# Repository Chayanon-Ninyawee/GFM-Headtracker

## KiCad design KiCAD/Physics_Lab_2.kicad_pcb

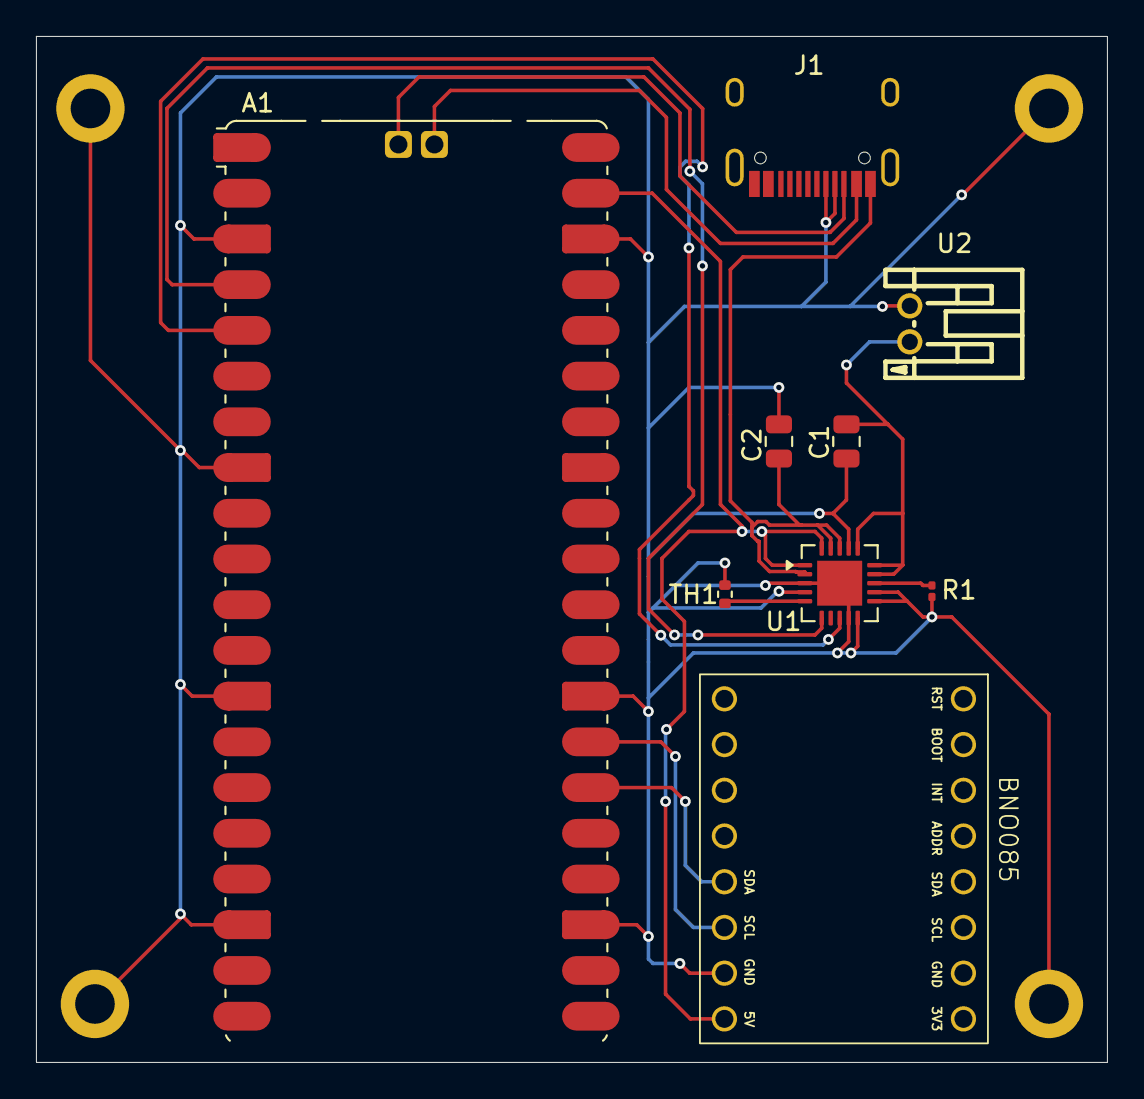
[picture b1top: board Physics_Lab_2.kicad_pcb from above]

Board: 2 copper layers, 59.5 x 57.0 mm, 9 parts (0 on the bottom side), 12 nets.

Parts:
A1: RaspberryPi_Pico_W; RaspberryPi_Pico_W_SMD
BNO085_Halley1: BNO085 Halley
C1: 4.7uF; C_0805_2012Metric
C2: 10uF; C_0805_2012Metric
J1: USB_C; HRO-TYPE-C-31-M-12
R1: 2K; R_0201_0603Metric
TH1: 10kΩ; R_0402_1005Metric
U1: MCP73871; QFN-20-1EP_4x4mm_P0.5mm_EP2.5x2.5mm
U2: S2B-PH-K-S-GW; CONN-TH_S2B-PH-K-S-GW

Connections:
GND: A1.3 (GND), A1.8 (GND), A1.13 (GND), A1.18 (GND), A1.23 (GND), A1.28 (GND), A1.38 (GND), BNO085_Halley1.15 (GND), C1.2, C2.1, J1.4 (GND), J1.5 (Shield), R1.1, TH1.1, U1.3 (SEL), U1.4 (PROG2), U1.9 (~TE), U1.10 (V_{SS}), U1.11 (V_{SS}), U1.12 (PROG3), U1.17 (CE), U1.21 (V_{SS}), U2.2
unnamed: A1.4 (GPIO2), U1.6 (~PG)
unnamed: A1.5 (GPIO3), U1.8 (STAT1/~LBO)
unnamed: A1.26 (GPIO20), BNO085_Halley1.13 (SDA)
unnamed: A1.27 (GPIO21), BNO085_Halley1.14 (SCL)
unnamed: A1.TP2 (USB_DM), J1.2 (D-)
unnamed: A1.TP3 (USB_DP), J1.3 (D+)
unnamed: A1.39 (VSYS), BNO085_Halley1.16 (5V), U1.1 (OUT), U1.20 (OUT)
unnamed: C2.2, J1.1 (VBUS), U1.2 (VPCC), U1.18 (IN), U1.19 (IN)
unnamed: R1.2, U1.13 (PROG1)
unnamed: TH1.2, U1.5 (THERM)
unnamed: C1.1, U1.14 (V_{BAT}), U1.15 (V_{BAT}), U1.16 (V_{BAT_SENSE}), U2.1

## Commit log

2026-02-10 chore(main): release 0.0.1
2026-02-10 feat: Add Raspberry Pi Pico W test code
2026-02-16 Add mounting holes and remove errors
2026-02-24 Fix merge conflict by pause
2026-02-24 Fix wiring to battery and grounding
2026-02-24 Add ordering placeholder text
2026-02-24 Add gerber and BOM files
2026-03-08 Add STEP File
2026-03-08 Move file to folder
2026-03-26 Update CAD File
2026-03-29 feat: Make usb work
2026-03-29 fix: Fix euler gimbal lock
2026-03-29 fix: Fix the lib folder name
